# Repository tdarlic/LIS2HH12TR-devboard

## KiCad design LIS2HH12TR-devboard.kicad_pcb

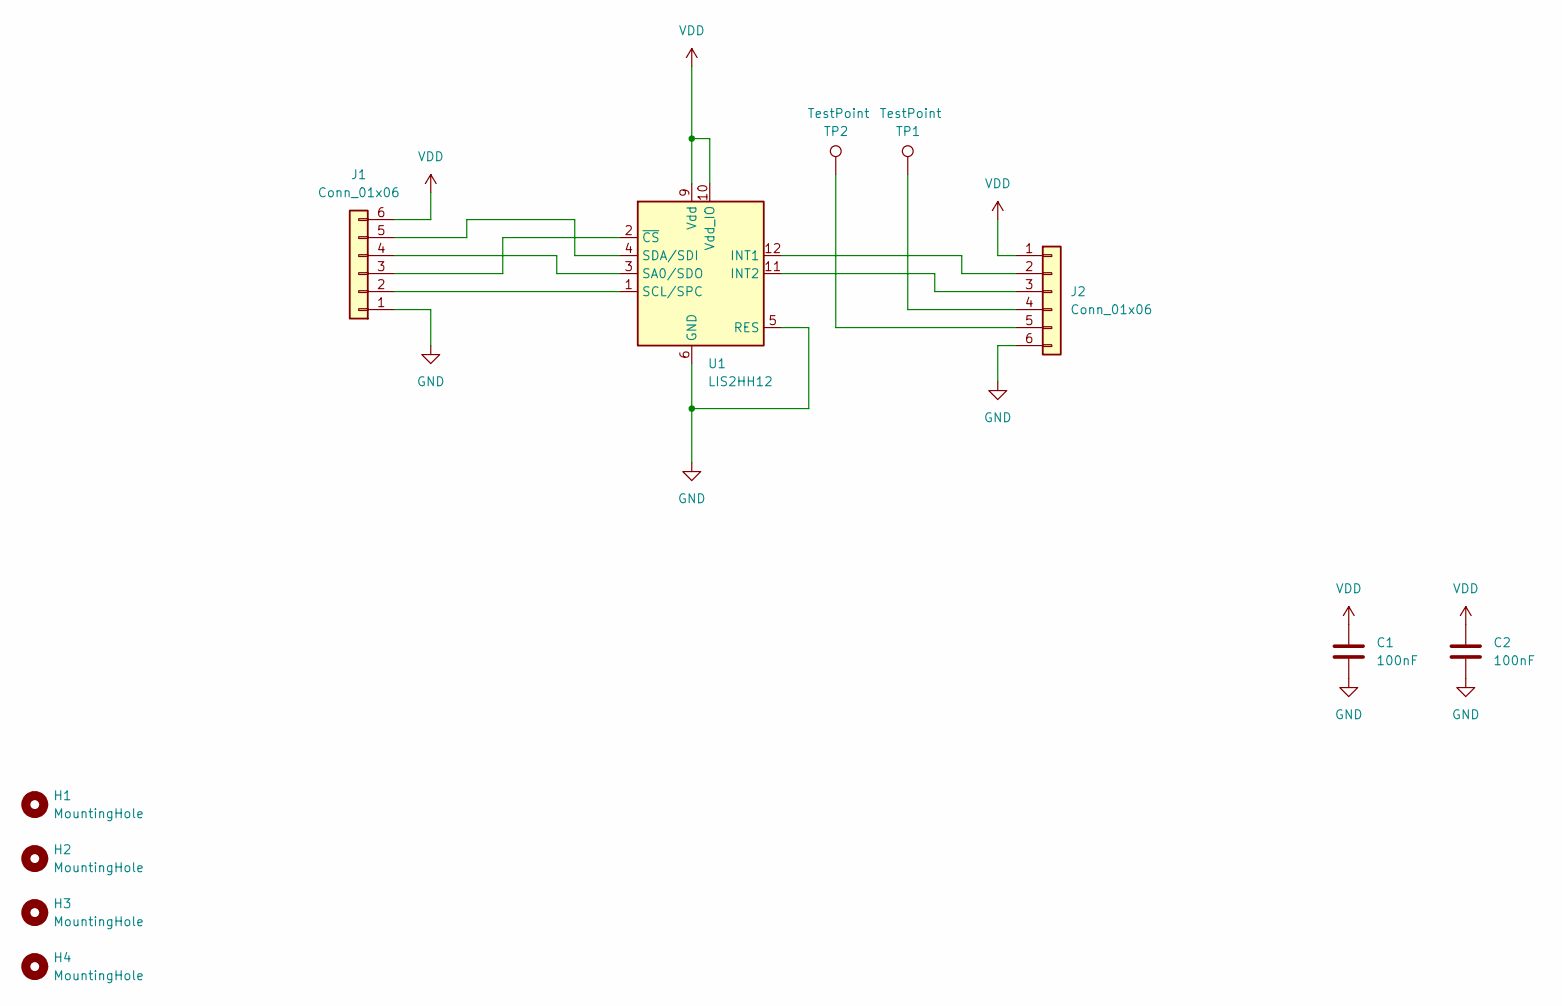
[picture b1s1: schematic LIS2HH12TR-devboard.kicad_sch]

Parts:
C1, C2: 100nF; C_0603_1608Metric
H1, H2, H3, H4: MountingHole; MountingHole_3.2mm_M3_DIN965
J1, J2: Conn_01x06; PinHeader_1x06_P2.54mm_Vertical
TP1, TP2: TestPoint; TestPoint_Pad_D2.0mm
U1: LIS2HH12; LGA-12_2x2mm_P0.5mm

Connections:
GND: C1.2, C2.2, J1.1, J2.6, U1.5 (RES), U1.6 (GND), U1.7 (GND), U1.8 (GND)
unnamed: J1.2, U1.1 (SCL/SPC)
unnamed: J1.3, U1.2 (~CS)
unnamed: J1.4, U1.3 (SA0/SDO)
unnamed: J1.5, U1.4 (SDA/SDI)
unnamed: J2.2, U1.12 (INT1)
unnamed: J2.3, U1.11 (INT2)
unnamed: J2.4, TP1.1
unnamed: J2.5, TP2.1
VDD: C1.1, C2.1, J1.6, J2.1, U1.9 (Vdd), U1.10 (Vdd_IO)

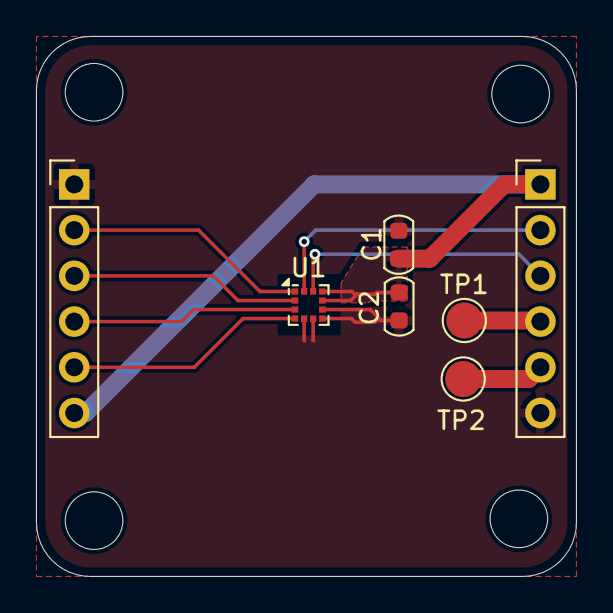
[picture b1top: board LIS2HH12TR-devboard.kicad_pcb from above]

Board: 2 copper layers, 30.0 x 30.0 mm, 11 parts (0 on the bottom side), 10 nets.

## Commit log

2025-02-17 Add lis2hh12-pid submodule into code dir
